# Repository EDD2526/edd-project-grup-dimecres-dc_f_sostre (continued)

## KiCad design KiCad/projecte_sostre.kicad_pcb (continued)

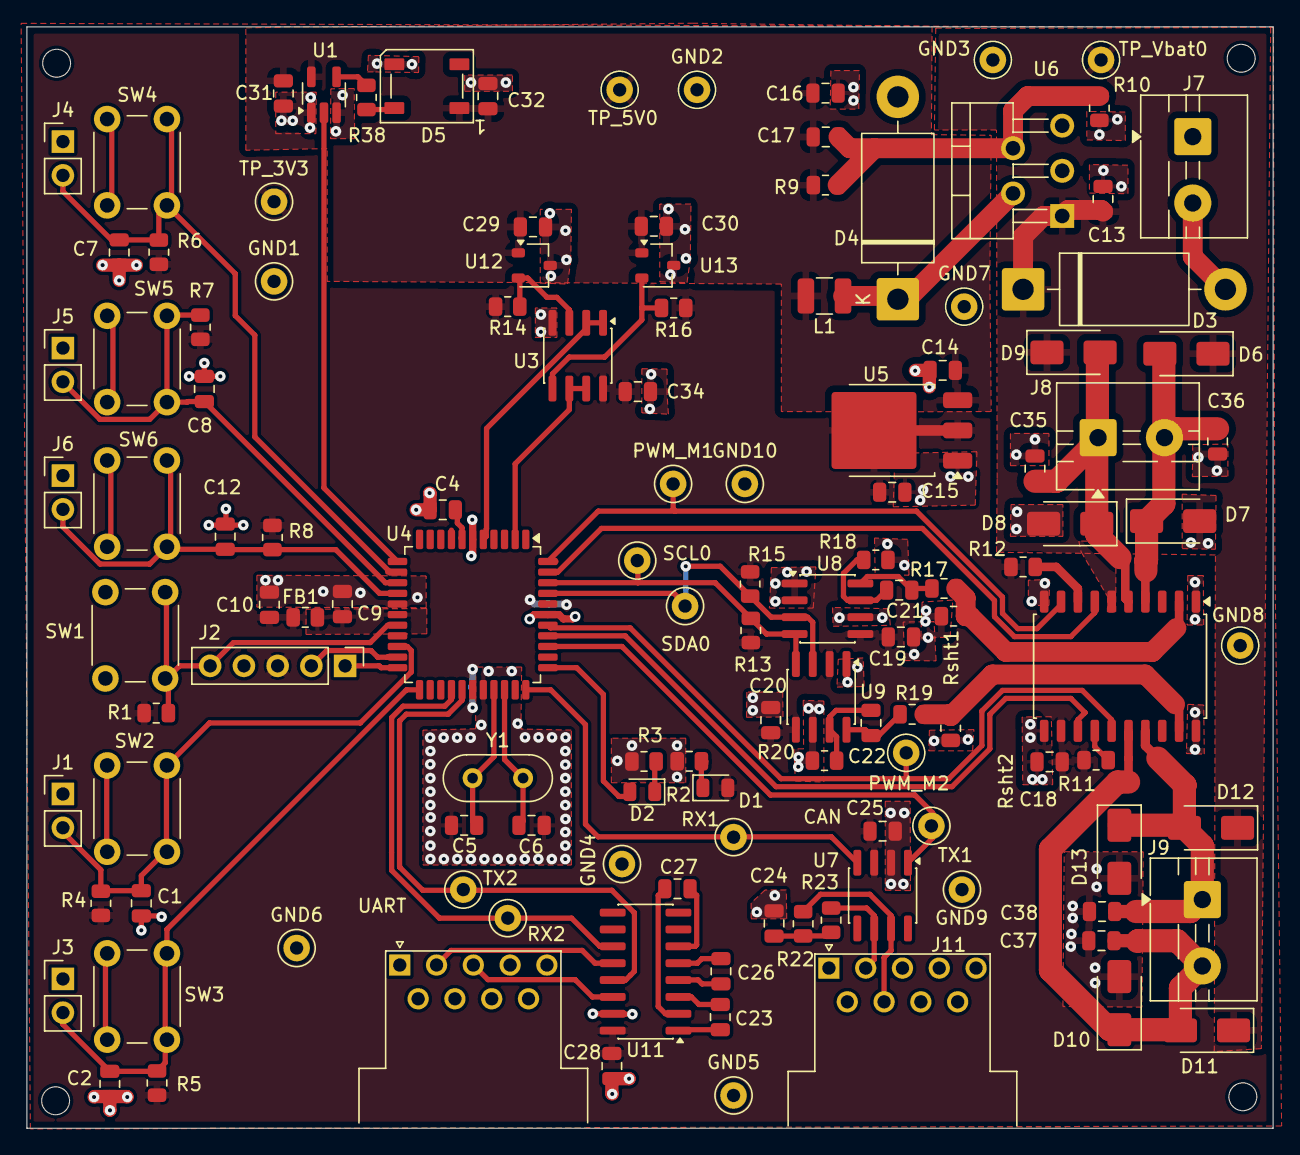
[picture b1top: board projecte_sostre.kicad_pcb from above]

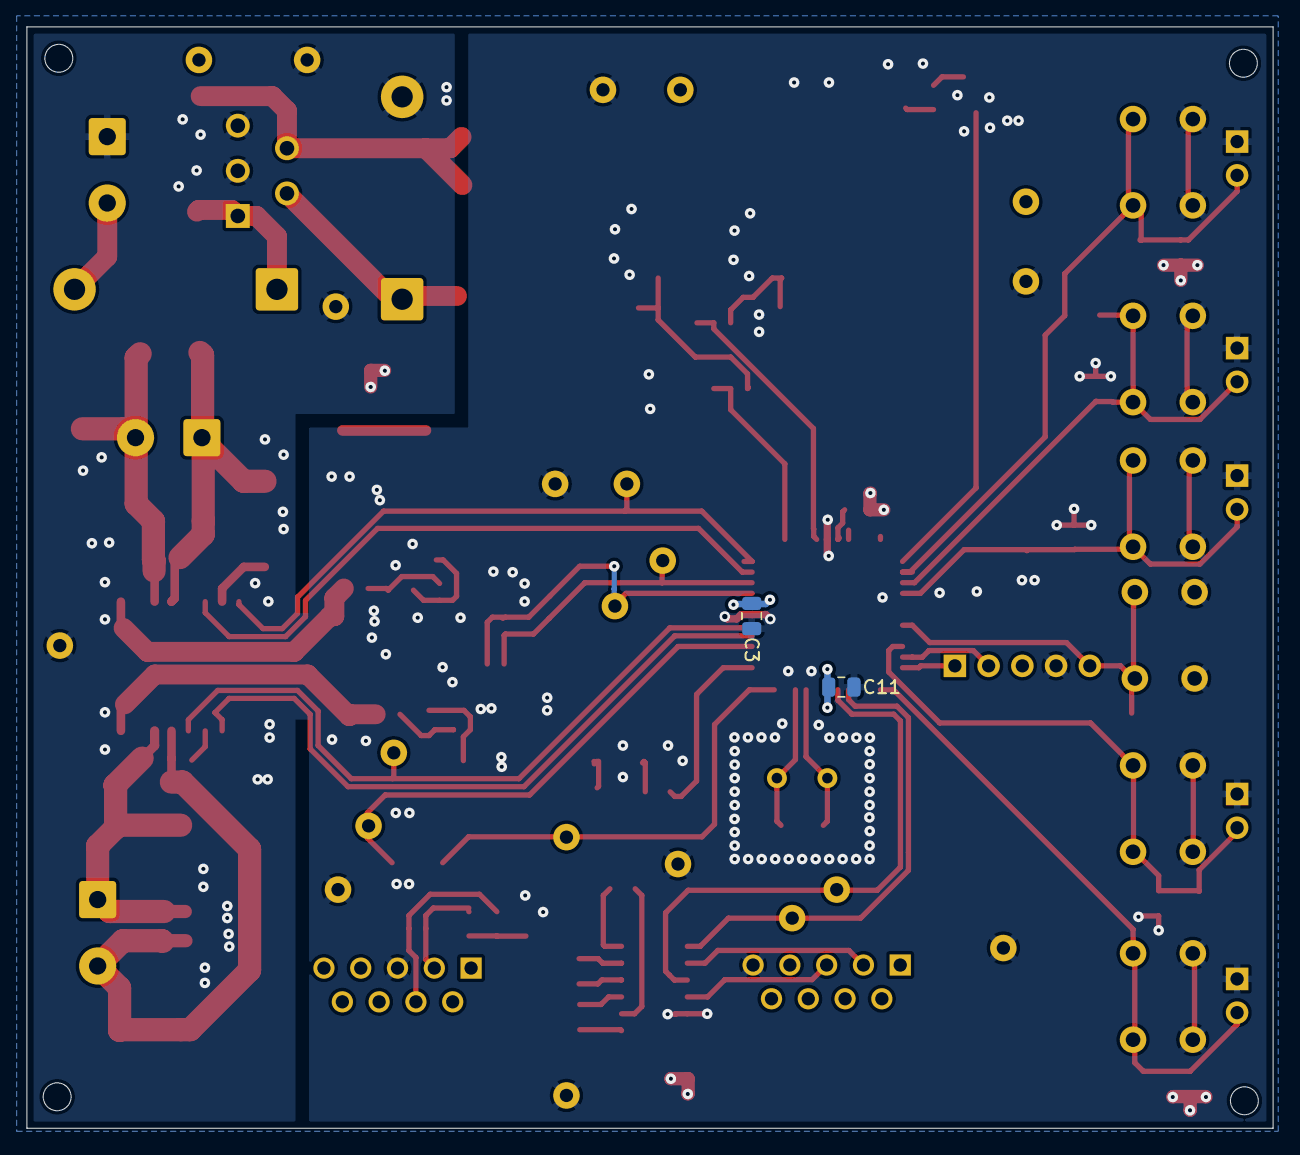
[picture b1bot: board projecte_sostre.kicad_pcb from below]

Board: 2 copper layers, 93.8 x 82.9 mm, 128 parts (2 on the bottom side), 62 nets.

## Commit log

2026-03-11 projecte kicad creat
2026-03-11 kicad creat
2026-03-11 esquematic modificat
2026-03-16 Backlink to CADLAB.io has been added.
2026-03-17 Començada part de micro i separacio de les 4 fases o grans grups de la PCB
2026-03-18 he afegit la part de potencia
2026-03-18 afegit part analogica
2026-03-18 Poner parte digital
2026-03-18 Subida para juntarlo todo 100 por 100
2026-03-18 Prueba 1
2026-03-23 Actualización ESquematico arreglandolo y corrigiendo fallos
2026-03-23 Nuevos cambios esquemativo v3
2026-03-24 Actualización de Esquematico, he puesto footprints y readme cambiado
2026-03-24 Añado el Readme
2026-03-24 Esquematico cambio en Sensor final de Carrera y Readme
2026-03-24 Esquematico acabado y readme estructura base y componentes acabado y puesto el DB.
2026-03-24 DG que se vea bien
2026-03-24 DB actualizado y ya se ve, definitivo a priori
2026-03-25 layout primer fet, queda canviar coses, pero una primera idea
2026-03-25 Cambios al esquematico por SEsión 3
2026-04-07 Cambio DG y pinzeladas ultimas al esquematico
2026-04-09 pujo el esquematico a medio hacer despues de hacer cambios para mejorar el 2o layout
2026-04-13 Test Points y Parte POwer ruteada de nuevo
2026-04-13 Voy a intentar mejorar el LED, sensor hall / sensor antiatrapamiento
2026-04-13 ultimos cambios, he puesto abajo sensor anti atrapamiento (usa AVDD y SENSOR_A y _B PROBLEMA porque atraviesa todo una linea muy ancha
2026-04-14 Sensor Hall y LED mas o menos definitivos
2026-04-20 Layout con pocos cables en capa Bot pero todavai hay que hacer cambios que nos dijo el Miercoles pasado
2026-04-26 Cambios Layout propuestos para mejorar posicionamiento
2026-04-27 Arreglo de algunos fallos DRC
2026-04-28 PCB casi acabada, despues de revisión de ayer 27/04 y cambio en componente CAN, que se vera reflejado en README y en DB
2026-04-28 Layout definitivo
2026-04-28 Readme ampliado
2026-04-28 Readme definitivo, correción de fallo de escritura y ahora DB si que se ve bien
2026-04-28 Readme ahora si que si deberia estar bien
2026-04-28 README finish finishez
2026-04-29 layout final
